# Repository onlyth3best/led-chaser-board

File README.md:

# led-chaser-board

<br/> what is it? a PCB with:
<br/> - resistors
<br/> - timers
<br/> - IC (integrated circuit) to control the LEDs
<br/> - LEDs
<br/> - capacitors

<br/> how does it work / how should you use it?
<br/> - *no firmware is required*, only a power source, if I recall correctly; the blinking should automatically start!

<br/> motivation for making it:
<br/> - as a beginner in terms of hardware projects, I thought it would be nice to make something simple for a moment before continuing onto more complicated PCB designs as well as other hardware things.

<br/> a mini project made with help from /stasis.hackclub.com/starter-projects/blinky
<br/>

<br/>
<br/> image of pcb and shematics:

<br/>

# BOM here:

| Reference             | Qty | Value       | Footprint                                         | Link                                                                 | Price    | Description                                  |
|-----------------------|-----|------------|---------------------------------------------------|----------------------------------------------------------------------|----------|----------------------------------------------|
| C1 | 1   | C_Polarized | Capacitor_THT:CP_Radial_D5.0mm_P2.00mm           | https://jlcpcb.com/partdetail/1875-0402B102K500NT/C1523            | 0.01 USD | Polarized capacitor |
| C2 | 1   | C           | Capacitor_THT:CP_Radial_D5.0mm_P2.00mm           | https://jlcpcb.com/partdetail/1875-0402B102K500NT/C1523            | 0.01 USD | Unpolarized capacitor |
| D1, D2, D3, D4, D5, D6, D7, D8, D9, D10 | 10  | LED         | LED_THT:LED_D3.0mm                               | https://sigmanortec.ro/en/led-5mm-white?SubmitCurrency=1&id_currency=3 | 0.07 USD | Light emitting diode |
| R1 | 1   | 470 Ω       | Resistor_THT:R_Axial_DIN0207_L6.3mm_D2.5mm_P7.62mm_Horizontal | https://jlcpcb.com/partdetail/1800-RS06K910JT/C1448 | 0.01 USD | Resistor   |
| R2 | 1   | 50 kΩ       | Resistor_THT:R_Axial_DIN0207_L6.3mm_D2.5mm_P7.62mm_Horizontal | https://jlcpcb.com/partdetail/1800-RS06K910JT/C1448 | 0.01 USD | Resistor   |
| R3 | 1   | 1 kΩ        | Resistor_THT:R_Axial_DIN0207_L6.3mm_D2.5mm_P7.62mm_Horizontal | https://jlcpcb.com/partdetail/1800-RS06K910JT/C1448 | 0.01 USD | Resistor   |
| U1 | 1   | NE555P      | Package_DIP:DIP-8_W7.62mm                        | https://www.mouser.co.uk/ProductDetail/Texas-Instruments/NE555P    | 0.58 USD | Precision Timer (555 compatible, PDIP-8) |
| U2 | 1   | 4017        | footprintsthiss:N16                              | https://uk.rs-online.com/web/p/counter-ics/7320691                 | 1.30 USD | Johnson Counter (10 outputs)  |
| - | -  | - | - | - | Total ~ 2.9 USD | -  |

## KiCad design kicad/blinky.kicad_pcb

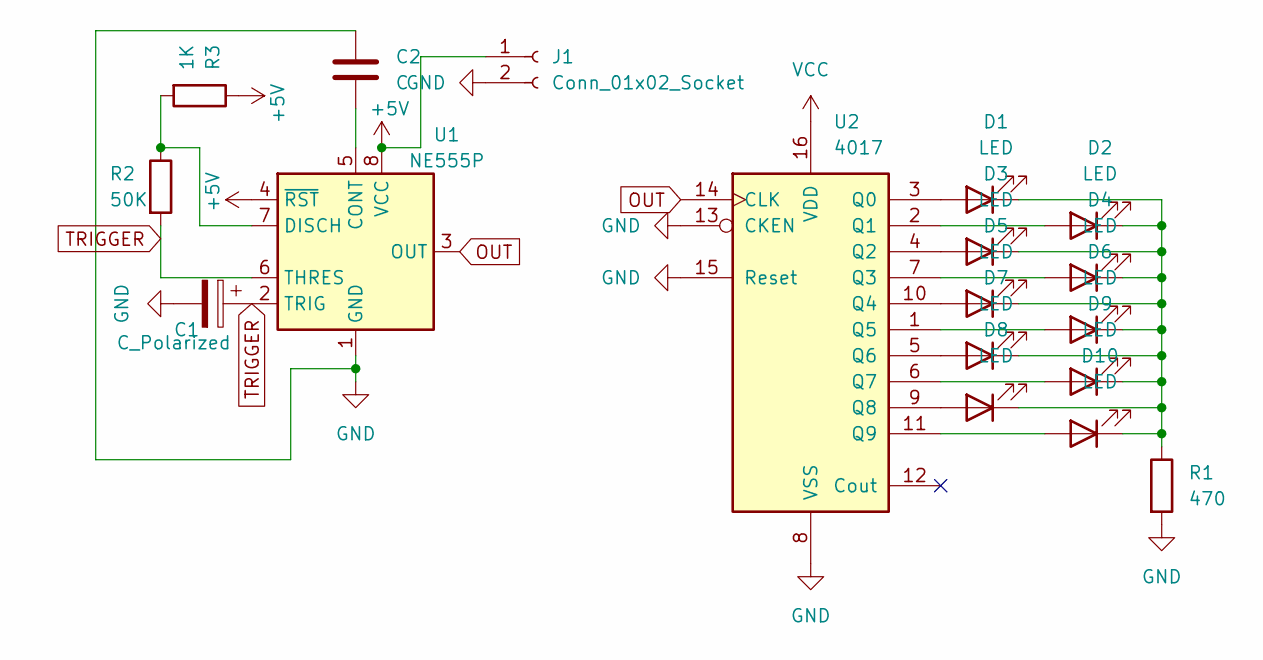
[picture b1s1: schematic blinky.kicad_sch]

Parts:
C1: C_Polarized; CP_Radial_D5.0mm_P2.00mm
C2: C; PinHeader_1x02_P2.54mm_Vertical
D1, D2, D3, D4, D5, D6, D7, D8, D9, D10: LED; LED_D3.0mm
J1: Conn_01x02_Socket; PinHeader_1x02_P2.54mm_Vertical
R1: 470; R_Axial_DIN0207_L6.3mm_D2.5mm_P7.62mm_Horizontal
R2: 50K; R_Axial_DIN0207_L6.3mm_D2.5mm_P7.62mm_Horizontal
R3: 1K; R_Axial_DIN0207_L6.3mm_D2.5mm_P7.62mm_Horizontal
U1: NE555P; DIP-8_W7.62mm
U2: 4017; N16

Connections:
+5V: J1.1, R3.1, U1.4 (~RST), U1.8 (VCC)
GND: C1.2, C2.1, J1.2, R1.2, U1.1 (GND), U2.8 (VSS), U2.13 (CKEN), U2.15 (Reset)
unnamed: D1.2 (A), U2.3 (Q0)
unnamed: D1.1 (K), D2.1 (K), D3.1 (K), D4.1 (K), D5.1 (K), D6.1 (K), D7.1 (K), D8.1 (K), D9.1 (K), D10.1 (K), R1.1
unnamed: D2.2 (A), U2.2 (Q1)
unnamed: D3.2 (A), U2.4 (Q2)
unnamed: D4.2 (A), U2.7 (Q3)
unnamed: D5.2 (A), U2.10 (Q4)
unnamed: D6.2 (A), U2.1 (Q5)
unnamed: D7.2 (A), U2.5 (Q6)
unnamed: D8.2 (A), U2.9 (Q8)
unnamed: D9.2 (A), U2.6 (Q7)
unnamed: D10.2 (A), U2.11 (Q9)
unnamed: C2.2, U1.5 (CONT)
unnamed: R2.1, R3.2, U1.7 (DISCH)
OUT: U1.3 (OUT), U2.14 (CLK)
TRIGGER: C1.1, R2.2, U1.2 (TRIG), U1.6 (THRES)
VCC: U2.16 (VDD)

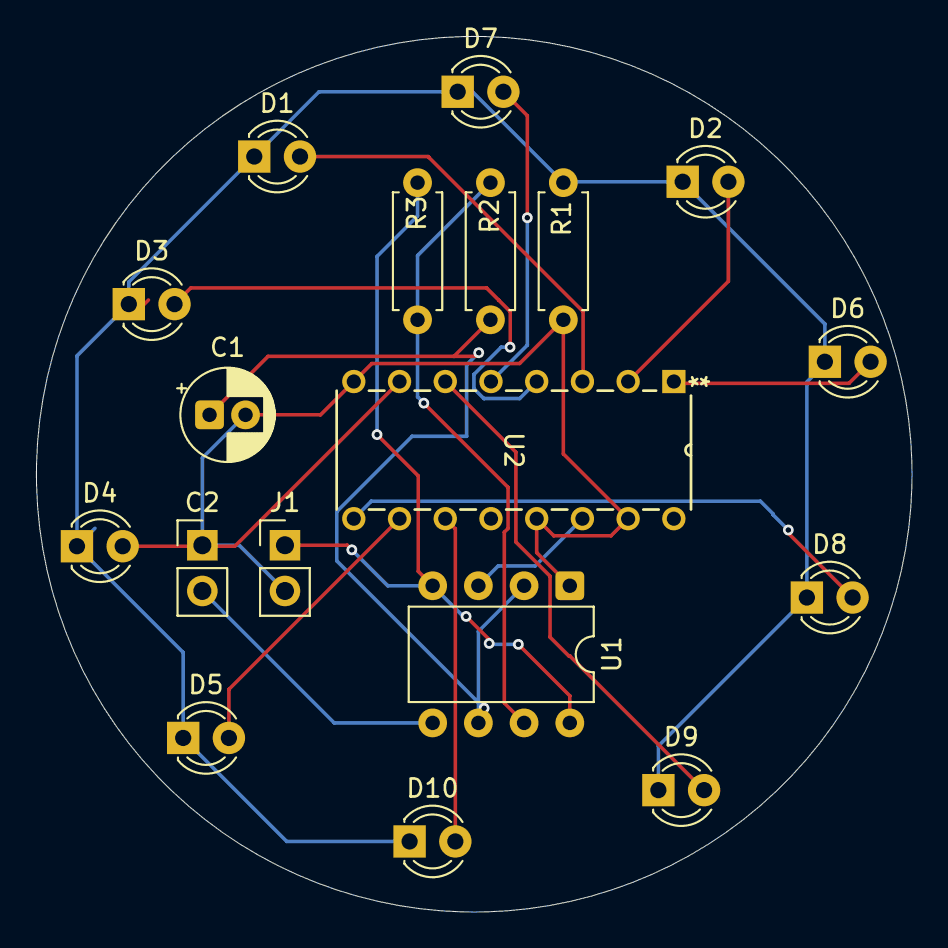
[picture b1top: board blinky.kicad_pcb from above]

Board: 2 copper layers, 48.6 x 48.6 mm, 18 parts (0 on the bottom side), 17 nets.

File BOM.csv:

"Reference","Qty","Value","DNP","Exclude from BOM","Exclude from Board","Footprint","Datasheet","Description"
"C1","1","C_Polarized","","","","Capacitor_THT:CP_Radial_D5.0mm_P2.00mm","","Polarized capacitor"
"C2","1","C","","","","","","Unpolarized capacitor"
"D1,D2,D3,D4,D5,D6,D7,D8,D9,D10","10","LED","","","","LED_THT:LED_D3.0mm","","Light emitting diode"
"R1","1","470","","","","Resistor_THT:R_Axial_DIN0207_L6.3mm_D2.5mm_P7.62mm_Horizontal","","Resistor"
"R2","1","50K","","","","Resistor_THT:R_Axial_DIN0207_L6.3mm_D2.5mm_P7.62mm_Horizontal","","Resistor"
"R3","1","1K","","","","Resistor_THT:R_Axial_DIN0207_L6.3mm_D2.5mm_P7.62mm_Horizontal","","Resistor"
"U1","1","NE555P","","","","Package_DIP:DIP-8_W7.62mm","http://www.ti.com/lit/ds/symlink/ne555.pdf","Precision Timers, 555 compatible, PDIP-8"
"U2","1","4017","","","","footprintsthiss:N16","http://www.intersil.com/content/dam/Intersil/documents/cd40/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","Johnson Counter ( 10 outputs )"

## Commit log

2026-04-28 Create test
